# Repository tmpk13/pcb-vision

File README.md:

# pcb-vision

Where on a board is the camera looking? pcb-vision reads a board's KiCad
design, watches a camera, and reports the pose of the picture on the
board as the frames come: the board point under the center of the
picture, how far the picture is turned, its scale, and the full map
from picture pixels to board millimeters. Pure Rust, no OpenCV.

| Directory | What |
| --- | --- |
| `crates/board` | `pcbv-board`: KiCad 5 to 10 `.kicad_pcb` reader, geometry, a raster of either side with a bare or a solder masked finish |
| `crates/vision` | `pcbv-vision`: spots in a picture, the search over the board's constellation, refinement to a homography, tracking, synthetic pictures |
| `crates/camera` | `pcbv-camera`: V4L2 capture, MJPEG and YUYV |
| `crates/app` | `pcbv`: the command line and the live viewer |
| `fixtures/boards` | boards with their ground truth dumped through KiCad's own `pcbnew`, for the parser tests |
| `tools` | `dump_board.py`: that ground truth |
| `docs` | [ARCHITECTURE.md](docs/ARCHITECTURE.md) |

## Quick start

Tools: a stable Rust toolchain and [mise](https://mise.jdx.dev). A V4L2
camera for the live view.

| Task | Does |
| --- | --- |
| `mise run live -- board.kicad_pcb --finish masked` | the live viewer on `/dev/video0`; `--camera`, `--size`, `--json`, `--no-window` |
| `mise run locate -- board.kicad_pcb photo.jpg --finish masked -o overlay.png --map map.png` | one picture: the pose, a marked up picture, the field of view on the board |
| `mise run render -- board.kicad_pcb -o board.png --style masked --finish masked` | draw a side |
| `mise run synth -- board.kicad_pcb -o shot.png --angle 30 --px-per-mm 25` | a camera picture made from the design, with its true pose |
| `mise run cameras` | the capture devices and their modes |
| `mise run test` | every suite |
| `mise run check` | clippy and the format check |

`--finish bare` is a board straight off a mill or laser, where all the
copper shows; `--finish masked` is a finished board, where only the
pads and whatever else the mask layer opens show. `--side back` looks at
the other side. Poses are reported in KiCad's board frame, millimeters
with x to the right and y down, for either side.

## How it works

The design is drawn as the camera would see the side, and the centroids
of its visible copper islands and of its drilled holes form a
constellation. A frame is looked at through one of three looks until one
locks: bright spots against a dark surround, copper by its chroma
against anything else, or dark holes. The spots are matched to the
constellation by trying similarities fixed by two spots and two
features, then the match is grown outward into a homography and tracked
from frame to frame. A pose counts only when it finds enough of the
features it says should be in view and explains enough of the spots on
the board.

`pcbv live --json` prints one line per frame for another program:
`state`, `center`, `angle_deg`, `mm_per_px`, `inliers`, `expected`,
`rms_mm`, `image_to_board` (a row major 3 by 3 map from full size pixels
to board millimeters) and `corners` (the board points under the four
picture corners).

## Limits

No lens model yet: a wide angle camera's distortion shows up as
residual at the picture edges. Silkscreen text is not drawn. A board
whose visible pattern is symmetric locks on either of its poses. One
board per frame.

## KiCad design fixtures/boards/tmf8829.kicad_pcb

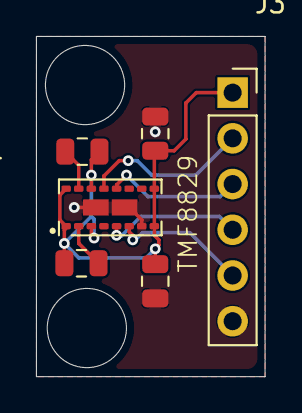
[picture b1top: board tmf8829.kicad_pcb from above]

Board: 2 copper layers, 12.7 x 18.9 mm, 6 parts (0 on the bottom side), 8 nets.

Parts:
C1, C2, C3, C4: 1.0uF; C_0805_2012Metric
J3: Conn_01x06; PinSocket_1x06_P2.54mm_Vertical
U1: TMF8829

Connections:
/CITO: J3.2, U1.13 (MISO/GPIO3)
/CLK: J3.3, U1.12 (SCLK/GPIO2)
/COTI: J3.4, U1.5 (MOSI/GPIO0)
/CSN: J3.5, U1.6 (CSN/GPIO1)
GND: C2.1, C4.1, J3.6, U1.7 (GND), U1.17 (GND), U1.18 (GND)
unnamed: C1.1, U1.2 (GNDC)
unnamed: C3.1, U1.15 (GNDV)
VCC: C1.2, C2.2, C3.2, C4.2, J3.1, U1.1 (VDDC), U1.3 (EN), U1.8 (VDD), U1.9 (VIO), U1.14 (VDDD), U1.16 (VDDV)

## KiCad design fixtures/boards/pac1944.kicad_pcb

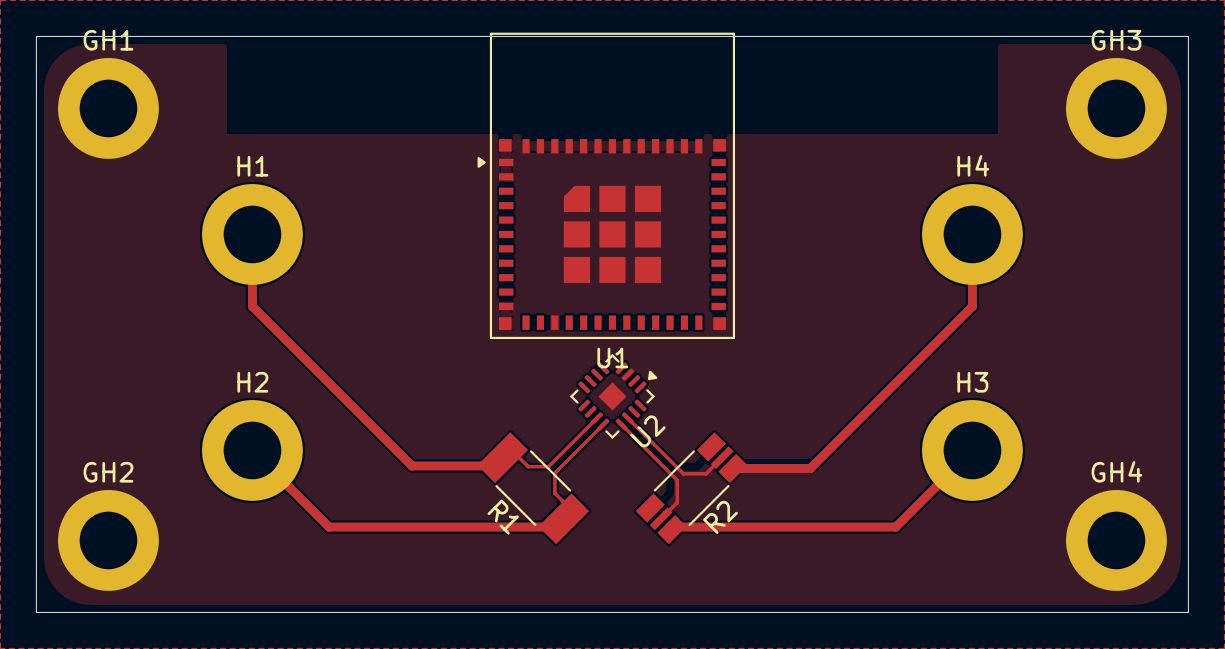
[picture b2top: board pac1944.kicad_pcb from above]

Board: 4 copper layers, 64.0 x 32.0 mm, 12 parts (0 on the bottom side), 10 nets.

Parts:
GH1, GH2, GH3, GH4: MountingHole_Pad; MountingHole_3.2mm_M3_DIN965_Pad
H1, H2, H3, H4: MountingHole_Pad; MountingHole_3.2mm_M3_DIN965_Pad
R1, R2: R_Shunt_US; R_2010_5025Metric_Pad1.40x2.65mm_HandSolder
U1: ESP32-C6-MINI-1
U2: PAC1944x-x4MX; VQFN-16-1EP_3x3mm_P0.5mm_EP1.1x1.1mm

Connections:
+3V3: U1.3 (3V3), U2.2 (V_{DD})
GND: GH1.1 (1_1), GH2.1 (1_1), GH3.1 (1_1), GH4.1 (1_1), U1.1 (GND), U1.2 (GND), U1.11 (GND), U1.14 (GND), U1.36 (GND), U1.37 (GND), U1.38 (GND), U1.39 (GND), U1.40 (GND), U1.41 (GND), U1.42 (GND), U1.43 (GND), U1.44 (GND), U1.45 (GND), U1.46 (GND), U1.47 (GND), U1.48 (GND), U1.49 (GND), U1.50 (GND), U1.51 (GND), U1.52 (GND), U1.53 (GND), U2.3 (GND), U2.17 (EP)
unnamed: H1.1 (1_1), R1.4
unnamed: H2.1 (1_1), R1.1
unnamed: H3.1 (1_1), R2.4
unnamed: H4.1 (1_1), R2.1
unnamed: R1.3, U2.11 (SENSE1+)
unnamed: R1.2, U2.12 (SENSE1-)
unnamed: R2.3, U2.13 (SENSE2+)
unnamed: R2.2, U2.14 (SENSE2-)
